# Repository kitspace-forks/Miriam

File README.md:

Miriam
========

Miriam is an open-source instrument for isothermal amplification reactions such as LAMP and realtime fluorescence detection. The costs per instrument are below 1000 USD, and our goal is to make it less expensive, more robust, and ready for volume production. It could be used as part of a test for Covid-19 😷.

**🔥 Update 2020 Oct 15 🔥** Updates are coming. We have built and tested a Miriam device and will be updating this repository with details soon. In the meantime, the new [BOM list](PCB/BOM) of the Covid-19 adapted Miriam is updated constantly during our test.

## User guide ##

View the [Miriam User Guide](https://docs.google.com/document/d/1WqGBbrccB8vQHHecIBe8Pv8aZ-rZUhXWWKjNA4fbFT0/edit?usp=sharing) as a Google Doc. Comments and suggestions are welcome.

## Help wanted

Currently, we are seeking help testing and improving the device. If you have skills circuit board layout, product design, software engineering, user interface design,  and thermal simulation, we could use your help. Furthermore, if you would like to collaborate to put this instrument to real world use, please file an issue or contact [Andrew Straw](<straw@bio.uni-freiburg.de>).

## License

Copyright Miroculus Inc.2016
Based on original work from Arduino (Sweden)

This documentation describes Open Hardware and is licensed under the CERN OHL v. 1.2.

Licensed under CERN OHL v.1.2

You may redistribute and modify this documentation under the terms of the [CERN OHL v.1.2.](http://ohwr.org/cernohl). This documentation is distributed WITHOUT ANY EXPRESS OR IMPLIED WARRANTY, INCLUDING OF MERCHANTABILITY, SATISFACTORY QUALITY AND FITNESS FOR A PARTICULAR PURPOSE. Please see the CERN OHL v.1.2 for applicable conditions

## Introduction

Miriam is optimized for the Syto 9 fluorescent intercalating DNA dye. (The original design was for [calcein dye](http://loopamp.eiken.co.jp/e/products/fluore/index.html). The selected LED is an angle SMD led with peak wavelength 461nm. The photodiode is an RGB photodiode most sensitive to green light. The optics also include an emission filter utilized in theatrical lighting.  The development and selection of components is further described in a [Master's thesis](http://lutpub.lut.fi/handle/10024/159386) done from miriam. 

**Figure 1.** LAMP reaction in 96 well plate. The reaction was performed in the center and corners of the 96 well plate to test heat uniformity.

In the performance testing of Miriam, the detection limit for DNA using LAMP as amplification platform has been 2amol in 10ul of sample (figure 1).

**Figure 2.** LAMP reaction with 2amol DNA input, fluorescence measured every 2 minutes (y, Normalized signal and x, cycle (2 min).

To report an issue, go to the [issues](http://github.com/strawlab/Miriam/issues) section

If you're interested in modifying or extending the Miriam platform, we strongly suggest you to send us an email discussing your ideas. That way you can coordinate with our team and others, giving your work a higher chance of being integrated into the official release.

## Design

The optics of Miriam plus are designed to support Syto9 + DNA. The emission and absorption spectra of Syto9 + DNA are represented in Figure 3.

**Figure 3.** Syto9+DNA emission and excitation spectra.

LEE filter 738 is used for blocking the excitation light. Whole optic design of Miriam plus is shown in Figure 4.

**Figure 4.** Optic design for Miriam plus to detect Syto9 + DNA.

The middle heating board and the LED and PD arrangements have been designed to support 96-well plates with the following dimensions (figure 5).

**Figure 5.** 96-well plate dimensions supported by Miriam

To control the heating of Miriam there are two heater PCBs. They have been designed so that in the middle is a 10 kohm SMD thermistor and the heat is generated by current flowing through the copper traces. These traces have been designed to be so long and narrow that they create an internal resistance of few ohms. The traces are closer to each other in the edges because heat is measured from the middle and the edges of the PCB boards meet ambient air and they need to produce more heat. (Figure 6.)

**Figure 6.** Heating plates, heat is generated by trace resistance. Right: The middle heater creating the temperature required for amplification (58-68 degrees C). Left: The top heater keeping vapor from condensing to the lid, kept at 80 degrees C. 

**Figure 6a.** The distribution of heat in the FR4 and Al heaters. FR4 heaters may work with small number of wells setup. For Miriam, we recommend using Al boards for better heat distribution.

Original Miriam design has 2.5 oC difference in temperature of the central wells and those on the far edge. Adding a heating wire on the edge of the lower heater can improve the uniformity (Fig. 6b). The temperature difference is reduced as low as 1oC or +/-0.5 oC by tuning the heat wire temperature (current) manually. An additional close-loop control for the heating wire would further improve the temperature uniformity.    

**Figure 6b.** Additional heat wire (left) helps to improve heat uniformity of the plate as in thermography images(right).

The heat uniformity of Miriam would be improved further by optimizing the heating traces of the heaters. Using a PCB thermal analysis software (Fig. 6C) with certain protocol for heat trace optimization would help to boost the design process.

**Figure 6c.** Heat distribution of the lower heater obtained from PCB thermal analysis software [(More detail of the analysis)](https://www.adam-research.de/en/2020/10/corona-forschung-mit-trm3/).

The detection of fluorescence is done with 96 LEDs and 96 photodiodes creating LED and photodiode PCBs. The LED peak wavelength is 470 nm and photodiode is a green RGB photodiode. The measured voltage is amplified with an operational amplifier to 0-5 V that is then converted by Arduino’s 8-bit ADC to be a numerical value. (figure 7.)

**Figure 7.** LED (left) and new photodiode (right) PCBs.

All of these boards are controlled by a shield that is directly mounted to the Arduino mega board (figure 8). The shield contains three MOSFETs to control LED board and the two heater boards, the required components to read the heat from the thermistors as well as a WIFI chip. The WIFI chip makes it possible for Arduino to be connected to a local WIFI and this way communicate autonomously to a web service.

**Figure 8.** The Arduino shield. 

Assembly
------------
3D print the printable parts under folder ["3D model"](3D%20Model), sand them if nescessary to make them align with each other. Assemble the boards as presented in the Figure 9. In the assembly cut with scissors the emission filter and glue to the filter holder.

**Figure 9.** Miriam assembly instruction. [High resolution version for printing](Miriam_assembly_guide.pdf) and [Video](https://youtu.be/ynIIGh6IMBA)

**Note:** All the cables used for Miriam must be "Opposite Side Contacts".
          For hand soldering, it is recommended to use solder paste and stencils for the sensor board. If it is possible, use reflow oven for the bottom side.
          
**Updated components:** The new [BOM list](PCB/BOM) of the Covid-19 adapted Miriam will be updated constantly during our test.

Software
------------
We just tested and improved the serial version of the software [Serial_003](Programs/Serial_003).

Improvement wish list
------------
A more robust type of connector can be considered. May change to 1mm pitch. 
Optimization for the traces of lower heater board to have uniformity heat distribution.

Credits
--------
The original Miriam is an open source project, supported by Miroculus in collaboration with Arduino (Sweden). The team was led by Juho Terrijarvi.

This version of Miriam has been improved by [Straw Lab](https://strawlab.org) to make it work with Syto-9 + DNA for potentially Covid-19 test.
Icon and image designed by Miroculus.

The PCB thermal analysis is performed by [ADAM research](https://www.adam-research.de/en/). 

Code of conduct
--------
Anyone who interacts with this software in any space, including but not limited
to this GitHub repository, must follow our [code of
conduct](code_of_conduct.md).

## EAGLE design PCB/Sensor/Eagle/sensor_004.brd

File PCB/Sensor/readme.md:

# Sensor_004
- Changed the order of power pins of the connector and the new footprint for new photodiode (TEMD6200FX01)

- material FR4
- 2 layer
- double sided assembly
- 1oz copper
- 1.6 mm thick
- Leadfree HAL
- Black soldermask
- White silkscreen

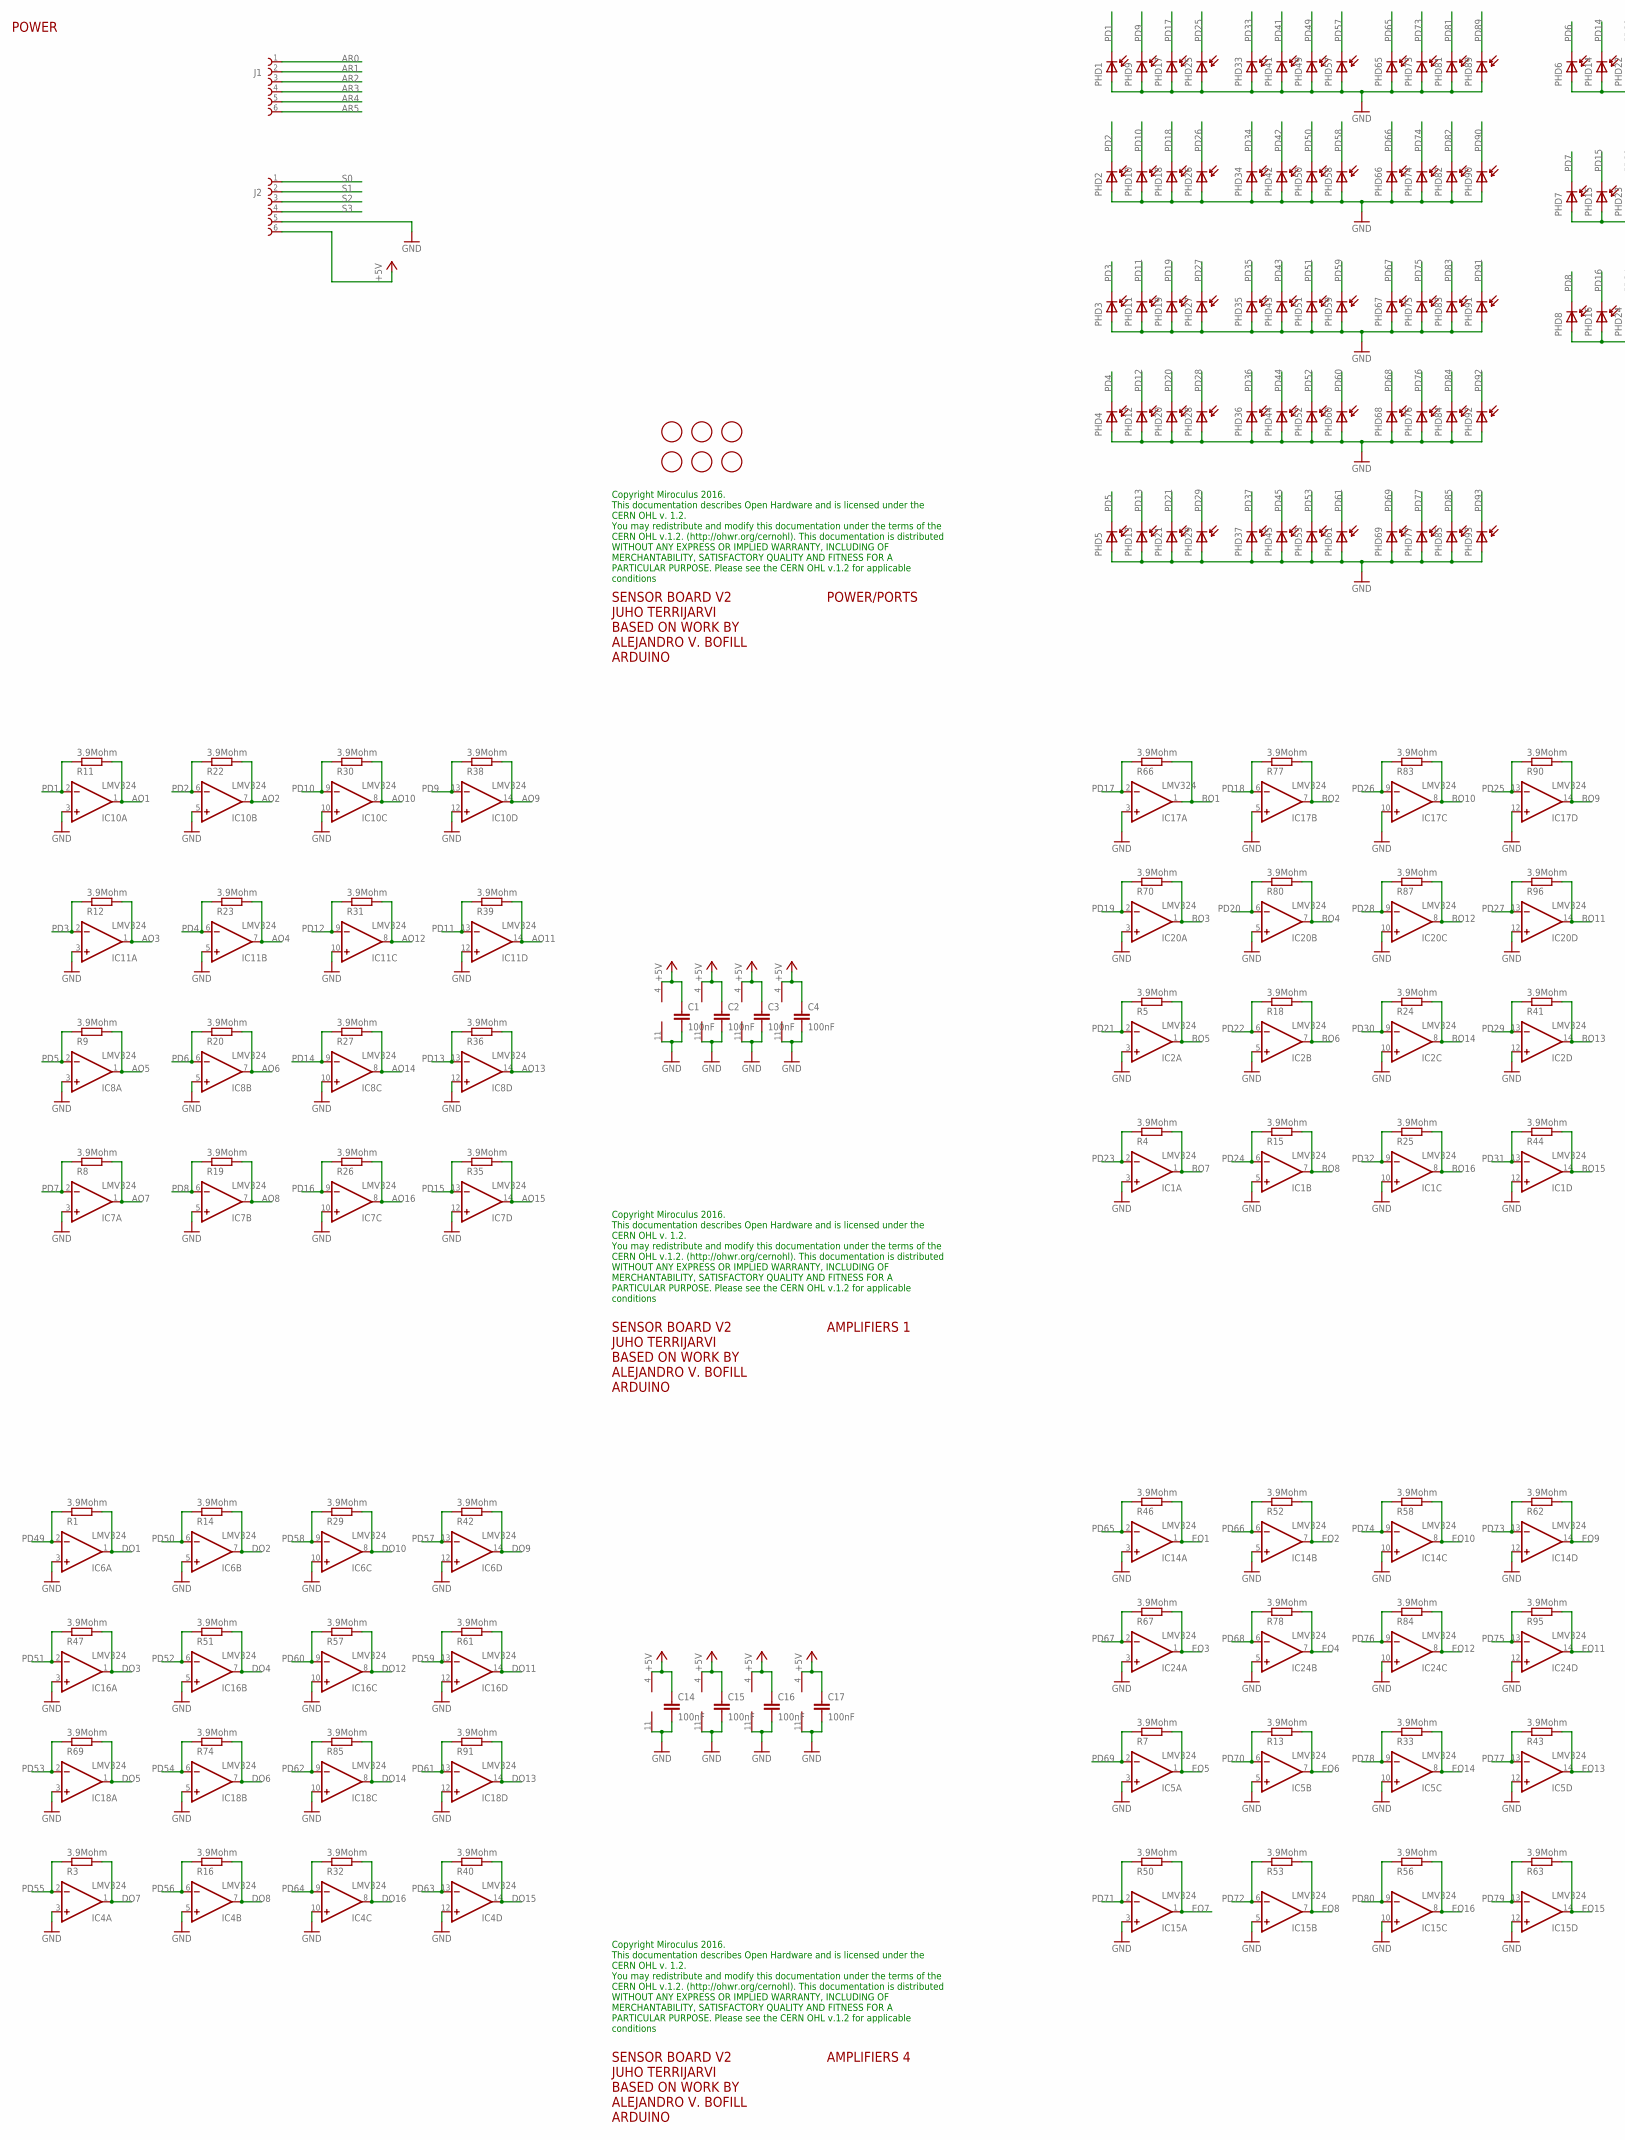
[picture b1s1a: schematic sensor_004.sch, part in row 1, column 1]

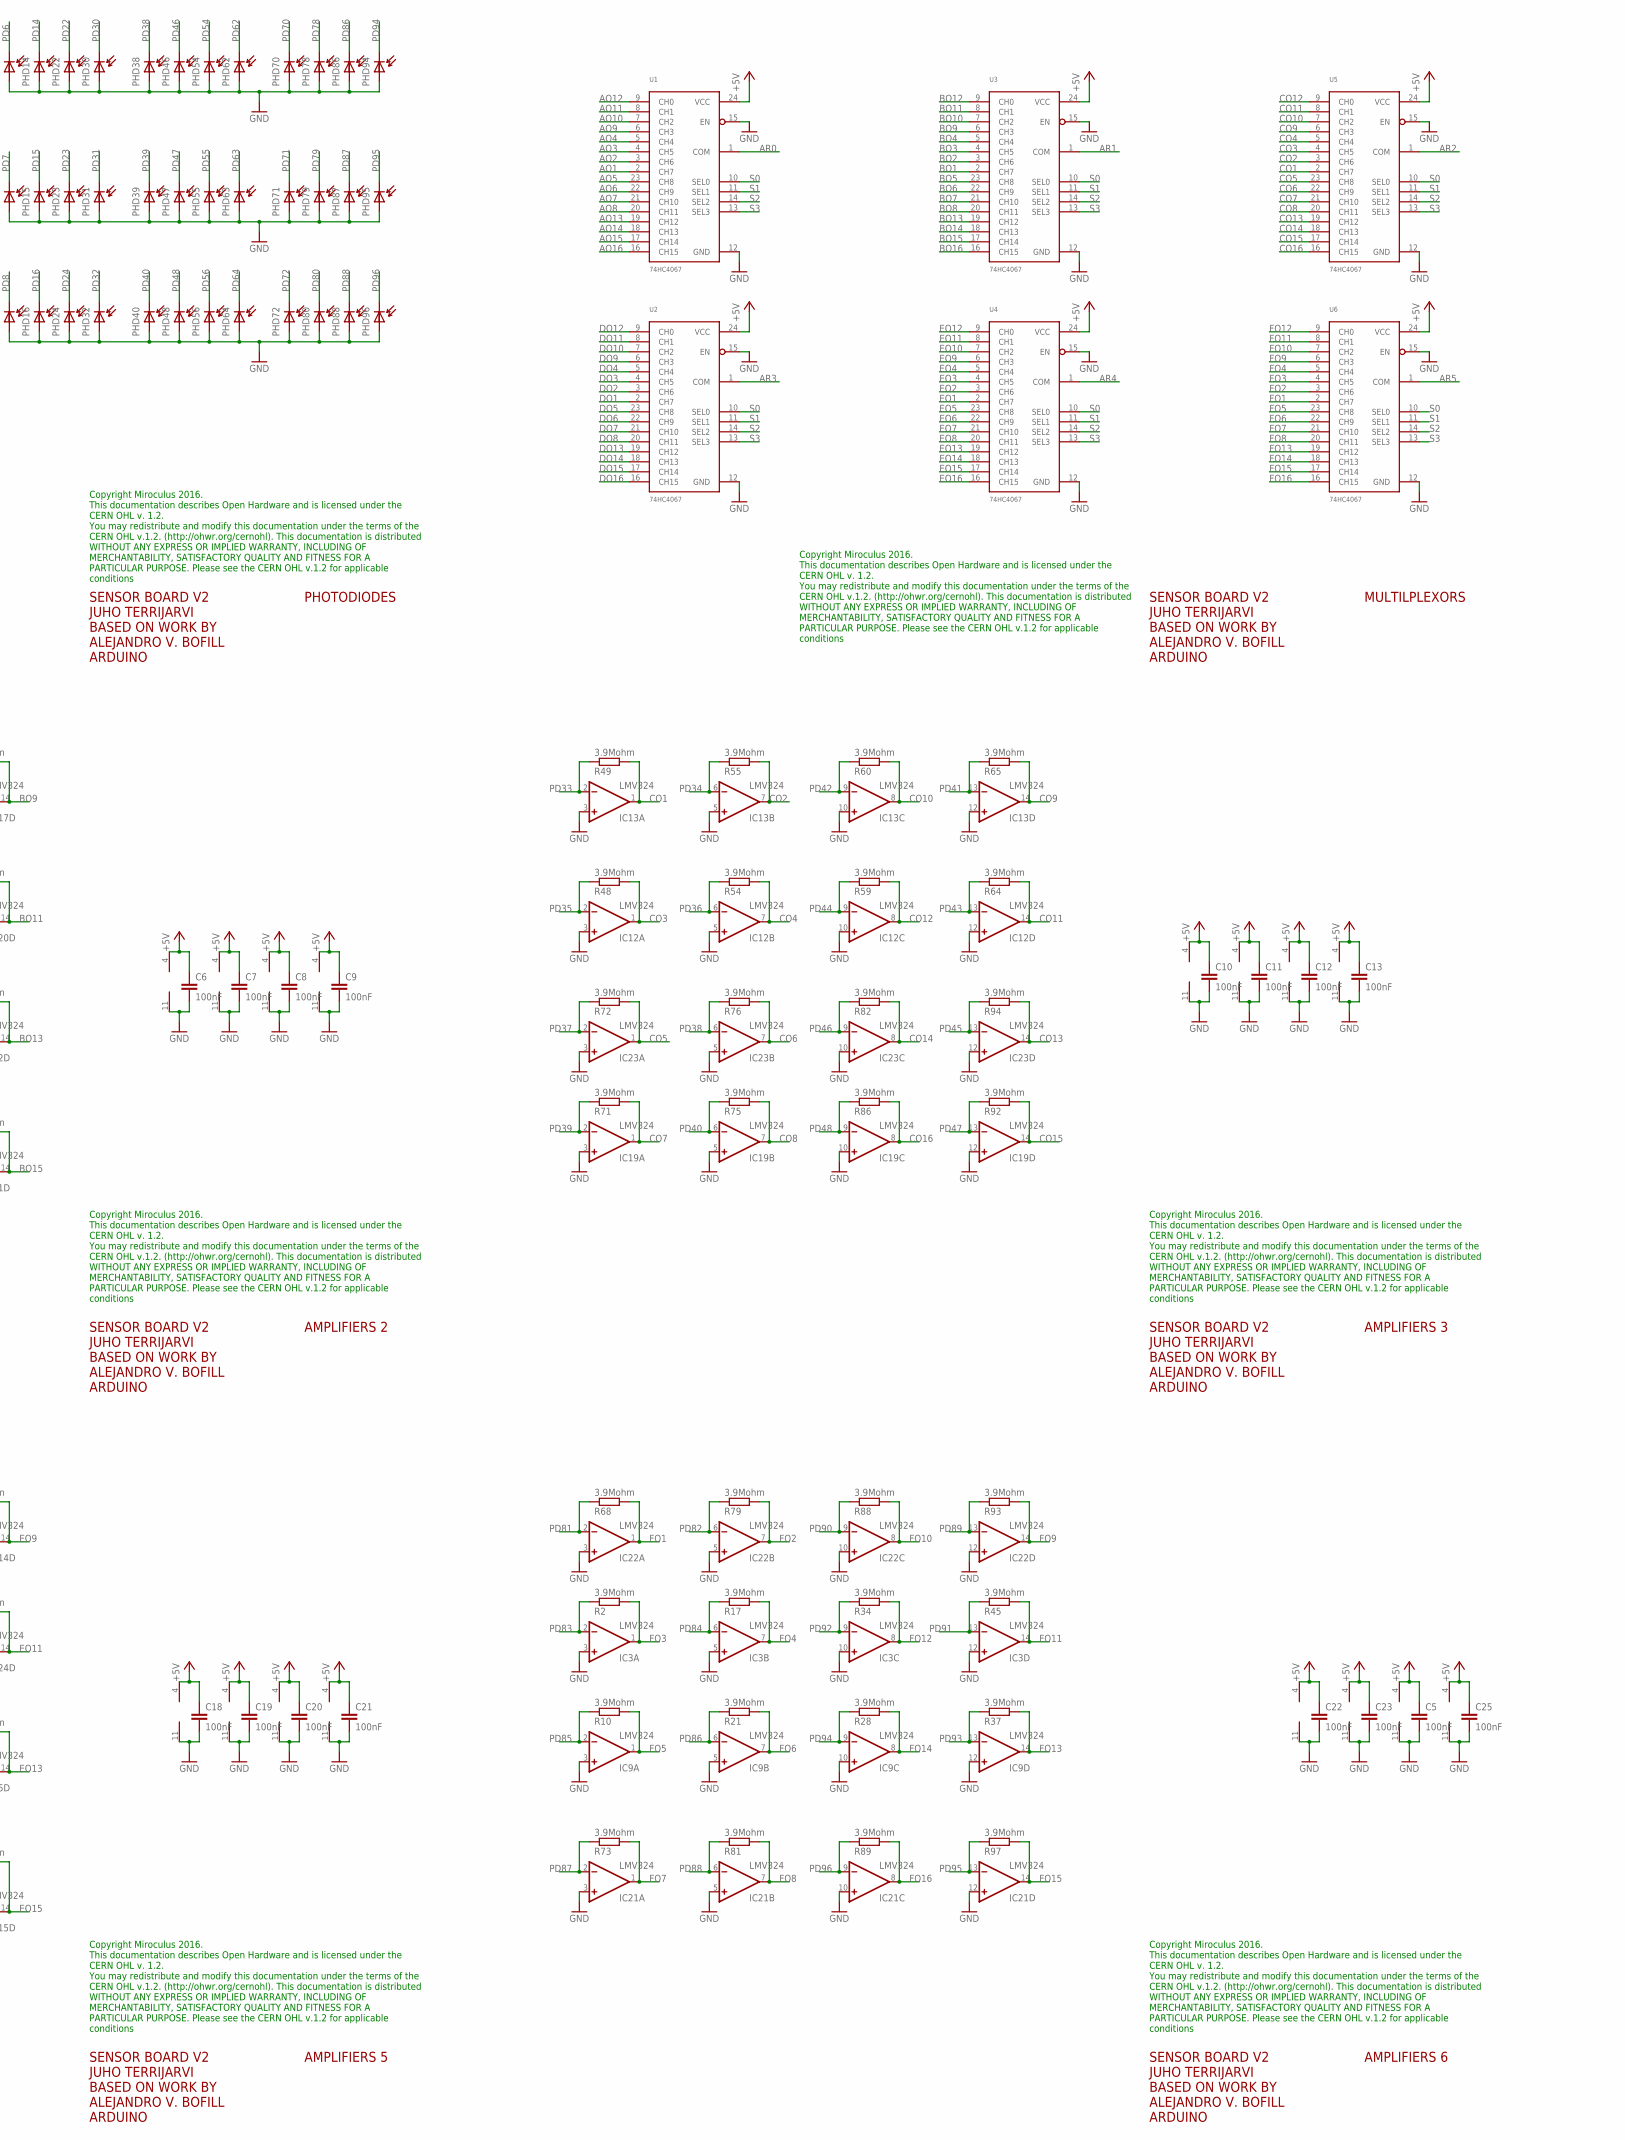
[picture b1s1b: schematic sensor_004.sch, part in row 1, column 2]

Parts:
C1, C2, C3, C4, C5, C6, C7, C8, C9, C10, C11, C12, C13, C14, C15, C16, C17, C18, C19, C20, C21, C22, C23, C25: 100nF; C0603
FD1, FD2, FD3, FD4, FD5, FD6: FIDUCIALMOUNT; FIDUCIA-MOUNT
IC1, IC2, IC3, IC4, IC5, IC6, IC7, IC8, IC9, IC10, IC11, IC12, IC13, IC14, IC15, IC16, IC17, IC18, IC19, IC20, IC21, IC22, IC23, IC24: LMV324; SO14
J1, J2: 68710614522
PHD1, PHD2, PHD3, PHD4, PHD5, PHD6, PHD7, PHD8, PHD9, PHD10, PHD11, PHD12, PHD13, PHD14, PHD15, PHD16, PHD17, PHD18, PHD19, PHD20, PHD21, PHD22, PHD23, PHD24, PHD25, PHD26, PHD27, PHD28, PHD29, PHD30, PHD31, PHD32, PHD33, PHD34, PHD35, PHD36, PHD37, PHD38, PHD39, PHD40, PHD41, PHD42, PHD43, PHD44, PHD45, PHD46, PHD47, PHD48, PHD49, PHD50, PHD51, PHD52, PHD53, PHD54, PHD55, PHD56, PHD57, PHD58, PHD59, PHD60, PHD61, PHD62, PHD63, PHD64, PHD65, PHD66, PHD67, PHD68, PHD69, PHD70, PHD71, PHD72, PHD73, PHD74, PHD75, PHD76, PHD77, PHD78, PHD79, PHD80, PHD81, PHD82, PHD83, PHD84, PHD85, PHD86, PHD87, PHD88, PHD89, PHD90, PHD91, PHD92, PHD93, PHD94, PHD95, PHD96: CLS15-22C/L213G/TR8; PD_2
R1, R2, R3, R4, R5, R7, R8, R9, R10, R11, R12, R13, R14, R15, R16, R17, R18, R19, R20, R21, R22, R23, R24, R25, R26, R27, R28, R29, R30, R31, R32, R33, R34, R35, R36, R37, R38, R39, R40, R41, R42, R43, R44, R45, R46, R47, R48, R49, R50, R51, R52, R53, R54, R55, R56, R57, R58, R59, R60, R61, R62, R63, R64, R65, R66, R67, R68, R69, R70, R71, R72, R73, R74, R75, R76, R77, R78, R79, R80, R81, R82, R83, R84, R85, R86, R87, R88, R89, R90, R91, R92, R93, R94, R95, R96, R97: 3.9Mohm; R0603
U1, U2, U3, U4, U5, U6: 74HC4067; SSOP24

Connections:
+5V: C1.1, C2.1, C3.1, C4.1, C5.1, C6.1, C7.1, C8.1, C9.1, C10.1, C11.1, C12.1, C13.1, C14.1, C15.1, C16.1, C17.1, C18.1, C19.1, C20.1, C21.1, C22.1, C23.1, C25.1, IC1.4 (V+), IC2.4 (V+), IC3.4 (V+), IC4.4 (V+), IC5.4 (V+), IC6.4 (V+), IC7.4 (V+), IC8.4 (V+), IC9.4 (V+), IC10.4 (V+), IC11.4 (V+), IC12.4 (V+), IC13.4 (V+), IC14.4 (V+), IC15.4 (V+), IC16.4 (V+), IC17.4 (V+), IC18.4 (V+), IC19.4 (V+), IC20.4 (V+), IC21.4 (V+), IC22.4 (V+), IC23.4 (V+), IC24.4 (V+), J2.6, U1.24 (VCC), U2.24 (VCC), U3.24 (VCC), U4.24 (VCC), U5.24 (VCC), U6.24 (VCC)
AO1: IC10.1 (OUT), R11.2, U1.2 (CH7)
AO2: IC10.7 (OUT), R22.2, U1.3 (CH6)
AO3: IC11.1 (OUT), R12.2, U1.4 (CH5)
AO4: IC11.7 (OUT), R23.2, U1.5 (CH4)
AO5: IC8.1 (OUT), R9.2, U1.23 (CH8)
AO6: IC8.7 (OUT), R20.2, U1.22 (CH9)
AO7: IC7.1 (OUT), R8.2, U1.21 (CH10)
AO8: IC7.7 (OUT), R19.2, U1.20 (CH11)
AO9: IC10.14 (OUT), R38.2, U1.6 (CH3)
AO10: IC10.8 (OUT), R30.2, U1.7 (CH2)
AO11: IC11.14 (OUT), R39.2, U1.8 (CH1)
AO12: IC11.8 (OUT), R31.2, U1.9 (CH0)
AO13: IC8.14 (OUT), R36.2, U1.19 (CH12)
AO14: IC8.8 (OUT), R27.2, U1.18 (CH13)
AO15: IC7.14 (OUT), R35.2, U1.17 (CH14)
AO16: IC7.8 (OUT), R26.2, U1.16 (CH15)
AR0: J1.1, U1.1 (COM)
AR1: J1.2, U3.1 (COM)
AR2: J1.3, U5.1 (COM)
AR3: J1.4, U2.1 (COM)
AR4: J1.5, U4.1 (COM)
AR5: J1.6, U6.1 (COM)
BO1: IC17.1 (OUT), R66.2, U3.2 (CH7)
BO2: IC17.7 (OUT), R77.2, U3.3 (CH6)
BO3: IC20.1 (OUT), R70.2, U3.4 (CH5)
BO4: IC20.7 (OUT), R80.2, U3.5 (CH4)
BO5: IC2.1 (OUT), R5.2, U3.23 (CH8)
BO6: IC2.7 (OUT), R18.2, U3.22 (CH9)
BO7: IC1.1 (OUT), R4.2, U3.21 (CH10)
BO8: IC1.7 (OUT), R15.2, U3.20 (CH11)
BO9: IC17.14 (OUT), R90.2, U3.6 (CH3)
BO10: IC17.8 (OUT), R83.2, U3.7 (CH2)
BO11: IC20.14 (OUT), R96.2, U3.8 (CH1)
BO12: IC20.8 (OUT), R87.2, U3.9 (CH0)
BO13: IC2.14 (OUT), R41.2, U3.19 (CH12)
BO14: IC2.8 (OUT), R24.2, U3.18 (CH13)
BO15: IC1.14 (OUT), R44.2, U3.17 (CH14)
BO16: IC1.8 (OUT), R25.2, U3.16 (CH15)
CO1: IC13.1 (OUT), R49.2, U5.2 (CH7)
CO2: IC13.7 (OUT), R55.2, U5.3 (CH6)
CO3: IC12.1 (OUT), R48.2, U5.4 (CH5)
CO4: IC12.7 (OUT), R54.2, U5.5 (CH4)
CO5: IC23.1 (OUT), R72.2, U5.23 (CH8)
CO6: IC23.7 (OUT), R76.2, U5.22 (CH9)
CO7: IC19.1 (OUT), R71.2, U5.21 (CH10)
CO8: IC19.7 (OUT), R75.2, U5.20 (CH11)
CO9: IC13.14 (OUT), R65.2, U5.6 (CH3)
CO10: IC13.8 (OUT), R60.2, U5.7 (CH2)
CO11: IC12.14 (OUT), R64.2, U5.8 (CH1)
CO12: IC12.8 (OUT), R59.2, U5.9 (CH0)
CO13: IC23.14 (OUT), R94.2, U5.19 (CH12)
CO14: IC23.8 (OUT), R82.2, U5.18 (CH13)
CO15: IC19.14 (OUT), R92.2, U5.17 (CH14)
CO16: IC19.8 (OUT), R86.2, U5.16 (CH15)
DO1: IC6.1 (OUT), R1.2, U2.2 (CH7)
DO2: IC6.7 (OUT), R14.2, U2.3 (CH6)
DO3: IC16.1 (OUT), R47.2, U2.4 (CH5)
DO4: IC16.7 (OUT), R51.2, U2.5 (CH4)
DO5: IC18.1 (OUT), R69.2, U2.23 (CH8)
DO6: IC18.7 (OUT), R74.2, U2.22 (CH9)
DO7: IC4.1 (OUT), R3.2, U2.21 (CH10)
DO8: IC4.7 (OUT), R16.2, U2.20 (CH11)
DO9: IC6.14 (OUT), R42.2, U2.6 (CH3)
DO10: IC6.8 (OUT), R29.2, U2.7 (CH2)
DO11: IC16.14 (OUT), R61.2, U2.8 (CH1)
DO12: IC16.8 (OUT), R57.2, U2.9 (CH0)
DO13: IC18.14 (OUT), R91.2, U2.19 (CH12)
DO14: IC18.8 (OUT), R85.2, U2.18 (CH13)
DO15: IC4.14 (OUT), R40.2, U2.17 (CH14)
DO16: IC4.8 (OUT), R32.2, U2.16 (CH15)
EO1: IC14.1 (OUT), R46.2, U4.2 (CH7)
EO2: IC14.7 (OUT), R52.2, U4.3 (CH6)
EO3: IC24.1 (OUT), R67.2, U4.4 (CH5)
EO4: IC24.7 (OUT), R78.2, U4.5 (CH4)
EO5: IC5.1 (OUT), R7.2, U4.23 (CH8)
EO6: IC5.7 (OUT), R13.2, U4.22 (CH9)
EO7: IC15.1 (OUT), R50.2, U4.21 (CH10)
EO8: IC15.7 (OUT), R53.2, U4.20 (CH11)
EO9: IC14.14 (OUT), R62.2, U4.6 (CH3)
EO10: IC14.8 (OUT), R58.2, U4.7 (CH2)
EO11: IC24.14 (OUT), R95.2, U4.8 (CH1)
EO12: IC24.8 (OUT), R84.2, U4.9 (CH0)
EO13: IC5.14 (OUT), R43.2, U4.19 (CH12)
EO14: IC5.8 (OUT), R33.2, U4.18 (CH13)
EO15: IC15.14 (OUT), R63.2, U4.17 (CH14)
EO16: IC15.8 (OUT), R56.2, U4.16 (CH15)
FO1: IC22.1 (OUT), R68.2, U6.2 (CH7)
FO2: IC22.7 (OUT), R79.2, U6.3 (CH6)
FO3: IC3.1 (OUT), R2.2, U6.4 (CH5)
FO4: IC3.7 (OUT), R17.2, U6.5 (CH4)
FO5: IC9.1 (OUT), R10.2, U6.23 (CH8)
FO6: IC9.7 (OUT), R21.2, U6.22 (CH9)
FO7: IC21.1 (OUT), R73.2, U6.21 (CH10)
FO8: IC21.7 (OUT), R81.2, U6.20 (CH11)
FO9: IC22.14 (OUT), R93.2, U6.6 (CH3)
FO10: IC22.8 (OUT), R88.2, U6.7 (CH2)
FO11: IC3.14 (OUT), R45.2, U6.8 (CH1)
FO12: IC3.8 (OUT), R34.2, U6.9 (CH0)
FO13: IC9.14 (OUT), R37.2, U6.19 (CH12)
FO14: IC9.8 (OUT), R28.2, U6.18 (CH13)
FO15: IC21.14 (OUT), R97.2, U6.17 (CH14)
FO16: IC21.8 (OUT), R89.2, U6.16 (CH15)
GND: C1.2, C2.2, C3.2, C4.2, C5.2, C6.2, C7.2, C8.2, C9.2, C10.2, C11.2, C12.2, C13.2, C14.2, C15.2, C16.2, C17.2, C18.2, C19.2, C20.2, C21.2, C22.2, C23.2, C25.2, IC1.3 (+IN), IC1.5 (+IN), IC1.10 (+IN), IC1.11 (V-), IC1.12 (+IN), IC2.3 (+IN), IC2.5 (+IN), IC2.10 (+IN), IC2.11 (V-), IC2.12 (+IN), IC3.3 (+IN), IC3.5 (+IN), IC3.10 (+IN), IC3.11 (V-), IC3.12 (+IN), IC4.3 (+IN), IC4.5 (+IN), IC4.10 (+IN), IC4.11 (V-), IC4.12 (+IN), IC5.3 (+IN), IC5.5 (+IN), IC5.10 (+IN), IC5.11 (V-), IC5.12 (+IN), IC6.3 (+IN), IC6.5 (+IN), IC6.10 (+IN), IC6.11 (V-), IC6.12 (+IN), IC7.3 (+IN), IC7.5 (+IN), IC7.10 (+IN), IC7.11 (V-), IC7.12 (+IN), IC8.3 (+IN), IC8.5 (+IN), IC8.10 (+IN), IC8.11 (V-), IC8.12 (+IN), IC9.3 (+IN), IC9.5 (+IN), IC9.10 (+IN), IC9.11 (V-), IC9.12 (+IN), IC10.3 (+IN), IC10.5 (+IN), IC10.10 (+IN), IC10.11 (V-), IC10.12 (+IN), IC11.3 (+IN), IC11.5 (+IN), IC11.10 (+IN), IC11.11 (V-), IC11.12 (+IN), IC12.3 (+IN), IC12.5 (+IN), IC12.10 (+IN), IC12.11 (V-), IC12.12 (+IN), IC13.3 (+IN), IC13.5 (+IN), IC13.10 (+IN), IC13.11 (V-), IC13.12 (+IN), IC14.3 (+IN), IC14.5 (+IN), IC14.10 (+IN), IC14.11 (V-), IC14.12 (+IN), IC15.3 (+IN), IC15.5 (+IN), IC15.10 (+IN), IC15.11 (V-), IC15.12 (+IN), IC16.3 (+IN), IC16.5 (+IN), IC16.10 (+IN), IC16.11 (V-), IC16.12 (+IN), IC17.3 (+IN), IC17.5 (+IN), IC17.10 (+IN), IC17.11 (V-), IC17.12 (+IN), IC18.3 (+IN), IC18.5 (+IN), IC18.10 (+IN), IC18.11 (V-), IC18.12 (+IN), IC19.3 (+IN), IC19.5 (+IN), IC19.10 (+IN), IC19.11 (V-), IC19.12 (+IN), IC20.3 (+IN), IC20.5 (+IN), IC20.10 (+IN), IC20.11 (V-), IC20.12 (+IN), IC21.3 (+IN), IC21.5 (+IN), IC21.10 (+IN), IC21.11 (V-), IC21.12 (+IN), IC22.3 (+IN), IC22.5 (+IN), IC22.10 (+IN), IC22.11 (V-), IC22.12 (+IN), IC23.3 (+IN), IC23.5 (+IN), IC23.10 (+IN), IC23.11 (V-), IC23.12 (+IN), IC24.3 (+IN), IC24.5 (+IN), IC24.10 (+IN), IC24.11 (V-), IC24.12 (+IN), J2.5, PHD1.1, PHD2.1, PHD3.1, PHD4.1, PHD5.1, PHD6.1, PHD7.1, PHD8.1, PHD9.1, PHD10.1, PHD11.1, PHD12.1, PHD13.1, PHD14.1, PHD15.1, PHD16.1, PHD17.1, PHD18.1, PHD19.1, PHD20.1, PHD21.1, PHD22.1, PHD23.1, PHD24.1, PHD25.1, PHD26.1, PHD27.1, PHD28.1, PHD29.1, PHD30.1, PHD31.1, PHD32.1, PHD33.1, PHD34.1, PHD35.1, PHD36.1, PHD37.1, PHD38.1, PHD39.1, PHD40.1, PHD41.1, PHD42.1, PHD43.1, PHD44.1, PHD45.1, PHD46.1, PHD47.1, PHD48.1, PHD49.1, PHD50.1, PHD51.1, PHD52.1, PHD53.1, PHD54.1, PHD55.1, PHD56.1, PHD57.1, PHD58.1, PHD59.1, PHD60.1, PHD61.1, PHD62.1, PHD63.1, PHD64.1, PHD65.1, PHD66.1, PHD67.1, PHD68.1, PHD69.1, PHD70.1, PHD71.1, PHD72.1, PHD73.1, PHD74.1, PHD75.1, PHD76.1, PHD77.1, PHD78.1, PHD79.1, PHD80.1, PHD81.1, PHD82.1, PHD83.1, PHD84.1, PHD85.1, PHD86.1, PHD87.1, PHD88.1, PHD89.1, PHD90.1, PHD91.1, PHD92.1, PHD93.1, PHD94.1, PHD95.1, PHD96.1, U1.12 (GND), U1.15 (EN), U2.12 (GND), U2.15 (EN), U3.12 (GND), U3.15 (EN), U4.12 (GND), U4.15 (EN), U5.12 (GND), U5.15 (EN), U6.12 (GND), U6.15 (EN)
PD1: IC10.2 (-IN), PHD1.2, R11.1
PD2: IC10.6 (-IN), PHD2.2, R22.1
PD3: IC11.2 (-IN), PHD3.2, R12.1
PD4: IC11.6 (-IN), PHD4.2, R23.1
PD5: IC8.2 (-IN), PHD5.2, R9.1
PD6: IC8.6 (-IN), PHD6.2, R20.1
PD7: IC7.2 (-IN), PHD7.2, R8.1
PD8: IC7.6 (-IN), PHD8.2, R19.1
PD9: IC10.13 (-IN), PHD9.2, R38.1
PD10: IC10.9 (-IN), PHD10.2, R30.1
PD11: IC11.13 (-IN), PHD11.2, R39.1
PD12: IC11.9 (-IN), PHD12.2, R31.1
PD13: IC8.13 (-IN), PHD13.2, R36.1
PD14: IC8.9 (-IN), PHD14.2, R27.1
PD15: IC7.13 (-IN), PHD15.2, R35.1
PD16: IC7.9 (-IN), PHD16.2, R26.1
PD17: IC17.2 (-IN), PHD17.2, R66.1
PD18: IC17.6 (-IN), PHD18.2, R77.1
PD19: IC20.2 (-IN), PHD19.2, R70.1
PD20: IC20.6 (-IN), PHD20.2, R80.1
PD21: IC2.2 (-IN), PHD21.2, R5.1
PD22: IC2.6 (-IN), PHD22.2, R18.1
PD23: IC1.2 (-IN), PHD23.2, R4.1
PD24: IC1.6 (-IN), PHD24.2, R15.1
PD25: IC17.13 (-IN), PHD25.2, R90.1
PD26: IC17.9 (-IN), PHD26.2, R83.1
PD27: IC20.13 (-IN), PHD27.2, R96.1
PD28: IC20.9 (-IN), PHD28.2, R87.1
PD29: IC2.13 (-IN), PHD29.2, R41.1
PD30: IC2.9 (-IN), PHD30.2, R24.1
PD31: IC1.13 (-IN), PHD31.2, R44.1
PD32: IC1.9 (-IN), PHD32.2, R25.1
PD33: IC13.2 (-IN), PHD33.2, R49.1
PD34: IC13.6 (-IN), PHD34.2, R55.1
PD35: IC12.2 (-IN), PHD35.2, R48.1
PD36: IC12.6 (-IN), PHD36.2, R54.1
PD37: IC23.2 (-IN), PHD37.2, R72.1
PD38: IC23.6 (-IN), PHD38.2, R76.1
PD39: IC19.2 (-IN), PHD39.2, R71.1
PD40: IC19.6 (-IN), PHD40.2, R75.1
PD41: IC13.13 (-IN), PHD41.2, R65.1
PD42: IC13.9 (-IN), PHD42.2, R60.1
PD43: IC12.13 (-IN), PHD43.2, R64.1
PD44: IC12.9 (-IN), PHD44.2, R59.1
PD45: IC23.13 (-IN), PHD45.2, R94.1
PD46: IC23.9 (-IN), PHD46.2, R82.1
PD47: IC19.13 (-IN), PHD47.2, R92.1
PD48: IC19.9 (-IN), PHD48.2, R86.1
PD49: IC6.2 (-IN), PHD49.2, R1.1
PD50: IC6.6 (-IN), PHD50.2, R14.1
PD51: IC16.2 (-IN), PHD51.2, R47.1
PD52: IC16.6 (-IN), PHD52.2, R51.1
PD53: IC18.2 (-IN), PHD53.2, R69.1
PD54: IC18.6 (-IN), PHD54.2, R74.1
PD55: IC4.2 (-IN), PHD55.2, R3.1
PD56: IC4.6 (-IN), PHD56.2, R16.1
PD57: IC6.13 (-IN), PHD57.2, R42.1
PD58: IC6.9 (-IN), PHD58.2, R29.1
PD59: IC16.13 (-IN), PHD59.2, R61.1
PD60: IC16.9 (-IN), PHD60.2, R57.1
PD61: IC18.13 (-IN), PHD61.2, R91.1
PD62: IC18.9 (-IN), PHD62.2, R85.1
PD63: IC4.13 (-IN), PHD63.2, R40.1
PD64: IC4.9 (-IN), PHD64.2, R32.1
PD65: IC14.2 (-IN), PHD65.2, R46.1
PD66: IC14.6 (-IN), PHD66.2, R52.1
PD67: IC24.2 (-IN), PHD67.2, R67.1
PD68: IC24.6 (-IN), PHD68.2, R78.1
PD69: IC5.2 (-IN), PHD69.2, R7.1
PD70: IC5.6 (-IN), PHD70.2, R13.1
PD71: IC15.2 (-IN), PHD71.2, R50.1
PD72: IC15.6 (-IN), PHD72.2, R53.1
PD73: IC14.13 (-IN), PHD73.2, R62.1
PD74: IC14.9 (-IN), PHD74.2, R58.1
PD75: IC24.13 (-IN), PHD75.2, R95.1
PD76: IC24.9 (-IN), PHD76.2, R84.1
PD77: IC5.13 (-IN), PHD77.2, R43.1
PD78: IC5.9 (-IN), PHD78.2, R33.1
PD79: IC15.13 (-IN), PHD79.2, R63.1
PD80: IC15.9 (-IN), PHD80.2, R56.1
PD81: IC22.2 (-IN), PHD81.2, R68.1
PD82: IC22.6 (-IN), PHD82.2, R79.1
PD83: IC3.2 (-IN), PHD83.2, R2.1
PD84: IC3.6 (-IN), PHD84.2, R17.1
PD85: IC9.2 (-IN), PHD85.2, R10.1
PD86: IC9.6 (-IN), PHD86.2, R21.1
PD87: IC21.2 (-IN), PHD87.2, R73.1
PD88: IC21.6 (-IN), PHD88.2, R81.1
PD89: IC22.13 (-IN), PHD89.2, R93.1
PD90: IC22.9 (-IN), PHD90.2, R88.1
PD91: IC3.13 (-IN), PHD91.2, R45.1
PD92: IC3.9 (-IN), PHD92.2, R34.1
PD93: IC9.13 (-IN), PHD93.2, R37.1
PD94: IC9.9 (-IN), PHD94.2, R28.1
PD95: IC21.13 (-IN), PHD95.2, R97.1
PD96: IC21.9 (-IN), PHD96.2, R89.1
S0: J2.1, U1.10 (SEL0), U2.10 (SEL0), U3.10 (SEL0), U4.10 (SEL0), U5.10 (SEL0), U6.10 (SEL0)
S1: J2.2, U1.11 (SEL1), U2.11 (SEL1), U3.11 (SEL1), U4.11 (SEL1), U5.11 (SEL1), U6.11 (SEL1)
S2: J2.3, U1.14 (SEL2), U2.14 (SEL2), U3.14 (SEL2), U4.14 (SEL2), U5.14 (SEL2), U6.14 (SEL2)
S3: J2.4, U1.13 (SEL3), U2.13 (SEL3), U3.13 (SEL3), U4.13 (SEL3), U5.13 (SEL3), U6.13 (SEL3)

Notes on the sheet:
SENSOR BOARD V2 JUHO TERRIJARVI BASED ON WORK BY ALEJANDRO V. BOFILL ARDUINO
POWER
POWER/PORTS
PHOTODIODES
AMPLIFIERS 1
AMPLIFIERS 2
AMPLIFIERS 3
AMPLIFIERS 4
AMPLIFIERS 5
AMPLIFIERS 6
MULTILPLEXORS
Copyright Miroculus 2016. This documentation describes Open Hardware and is licensed under the CERN OHL v. 1.2. You may redistribute and modify this documentation under the terms of the CERN OHL v.1.2. (http://ohwr.org/cernohl). This documentation is distributed WITHOUT ANY EXPRESS OR IMPLIED WARRA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

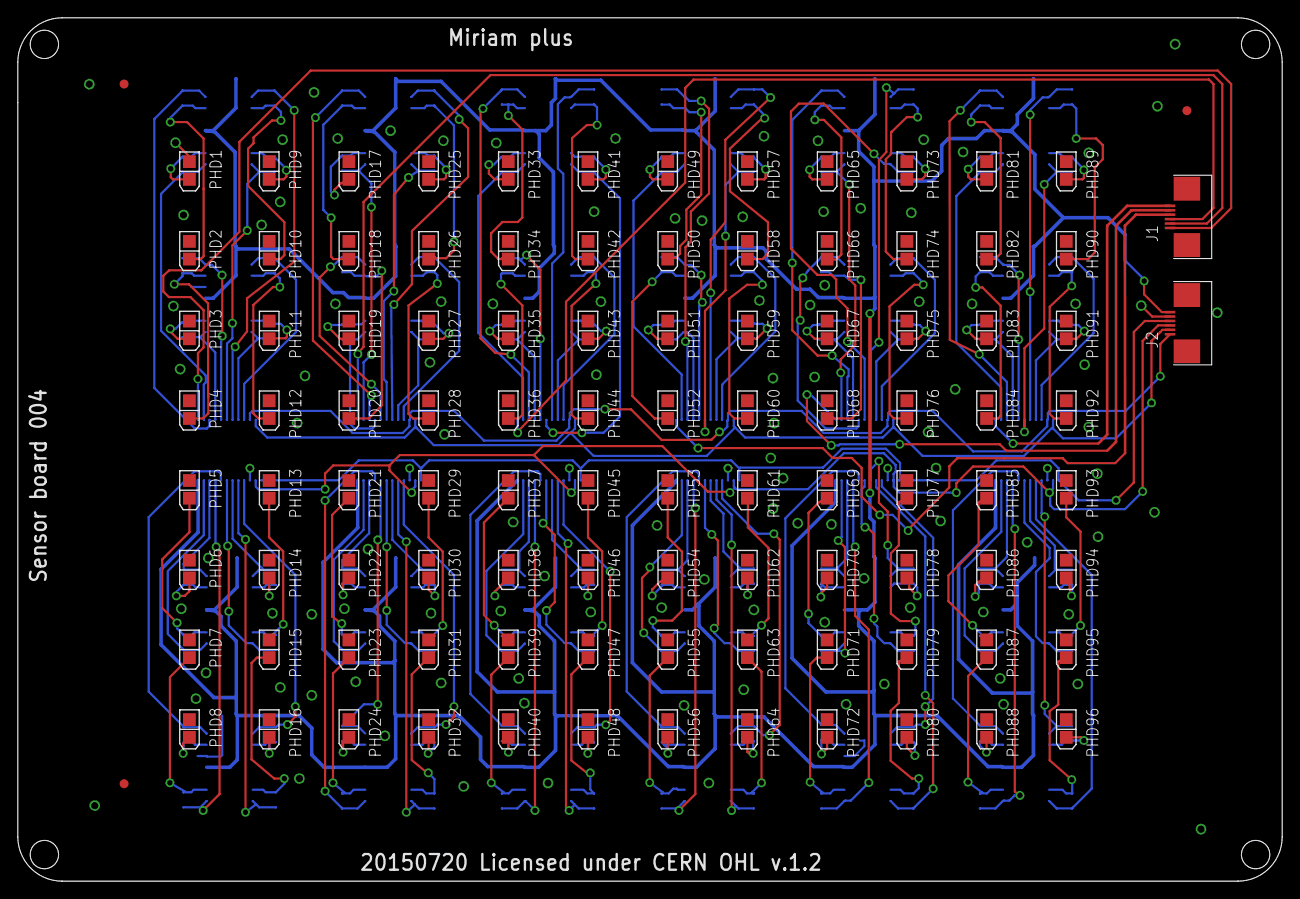
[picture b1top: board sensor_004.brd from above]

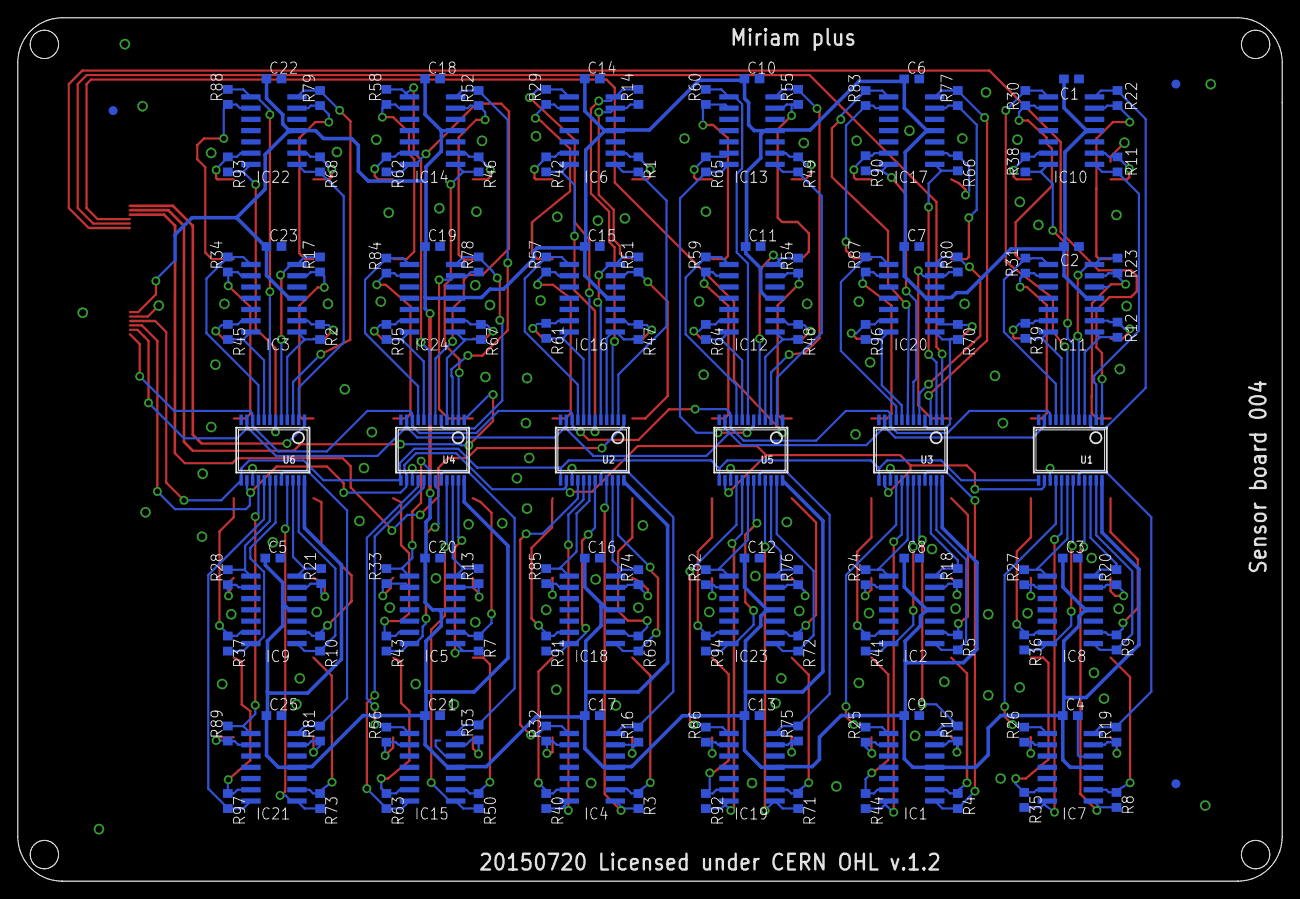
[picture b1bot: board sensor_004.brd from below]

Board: 2 copper layers, 142.8 x 97.5 mm, 254 parts (153 on the bottom side), 204 nets.

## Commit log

2020-08-27 autofill cell names A1->H12; change the hardcoded time between the readouts
2020-08-27 ignore .vs, obj. debug, bin folders
2020-08-28 reverse columns order on the plate (was incorrect)
2020-08-30 sensor2 wiring and FR4 heaters
2020-09-01 rearrange columns differently
    sequence from serial port: A11,A12,A9,A10,....,A1,A2, ...
2020-09-03 added the inter-measure interval setting (in seconds)
2020-09-03 write time of measurement to csv file
2020-09-03 reading from csv works (now filename is hardcoded, and the csv is assumed to be correctly formatted
2020-09-04 well names are stored in .cells.tsv file near the exe; added buttons to autofill and clear all names
2020-09-07 save csv to the app folder with filename miriam_datetime.csv
2020-09-09 update optic design for Syto9+DNA
2020-10-01 change sensor board and case
2020-10-01 add heat distribution
2020-10-08 make the settings persistent (store in app settings)
2020-10-08 ignore .cells.tsv file (generated automatically)
2020-10-08 beutify plot
    Yellow color replaced by Chocolate; the figure panel is resized with the form
2020-10-08 built release for the last changes
2020-10-08 remove unnecessary file
2020-10-15 add link to code of conduct
2020-10-15 fix layout
2020-10-15 add heat uniformity
2020-10-15 add heat_simulation
2020-10-22 added new arduino file
2020-10-22 cancel heating on exit
2020-10-23 ino:changed the temperature readout formula for A11 (TH_EXTRA)
2020-10-23 ino: changed order of 'i' output to be backward compatible
2020-10-23 fix typo
2020-10-23 reading temperatures with dicts, refactor arduino commands
2020-10-23 changed design for additional sensors; more refactoring for arduino readouts
2020-10-30 (ino) changed linear correction in temperature calculation
2020-10-30 Set EXTRA_HEAT to MANUAL when stop heating
2020-11-02 serial005.ino: with sound alarm and status LED (not finished)
2020-11-04 ino: extract mystatusled class description
2020-11-04 ino: editable box temperature threshold
2020-11-04 fix cancel on exit
2020-11-04 changed icon
2020-11-05 rebuild
2020-11-06 link to user guide in README
2020-11-06 RT-LAMP with Miriam flow
2020-11-06 Add assembly guide and new box
2020-11-06 correct link
2020-11-09 update BOM list
2020-11-13 fix heat canceling
2020-11-13 added box temperature threshold setting
2020-11-13 changed default settings
2020-11-19 cleaning attempt
2020-11-19 rebuilt with new icon; remove unnecessary files
2020-11-19 change calibration function of the thermistor
2020-11-25 make arduino PID_v1 library comply with spec
    See https://arduino.github.io/arduino-cli/latest/library-specification/
2020-11-25 update BOM
2020-11-25 change GUI figure
2020-11-25 replaced icon
2020-11-25 fixed programs readme
2020-11-25 Update SW/FW combinations in Serial Readme
2020-11-25 add continuous integration using github actions
    So far, this builds the Windows program and the Arduino firmware.
2020-11-25 add link to CI build in README
2020-11-28 adjust figure posiiton
2020-11-28 update BOM link
2020-12-02 write to csv live, removed last comma from all rows
2020-12-04 add melting function
2020-12-07 update BOM readme
2020-12-08 + form with melting settings; storing them in app settings; melting func not tested in reality; ino: add melting to list of states
2020-12-08 fixed filename format to yyyymmdd...
2020-12-09 fix melting stopping
2020-12-09 fixed float convertion bug; add tolerance parameter for melting
2020-12-09 ci: store artifact attempt
2020-12-09 rearrange for better time intervals
2020-12-09 +setting melting on/off
2020-12-11 fix temperature threshold check
2020-12-14 update melting tune
2020-12-22 added the controls to the form
2020-12-28 moved measurement settings
2020-12-29 moved folder setting
2020-12-29 + filename prefix setting
2021-01-11 update melt tuning
2021-01-11 start melting commands sequence changed
2021-01-12 add melt_init
2021-01-12 add melt init on software side
2021-01-12 debug arduino artifact building
2021-01-12 update name of zip file created in build step
2021-01-12 update job names
2021-01-12 Add PID output values to CSV
2021-01-12 Remove .exe file
    This executable is now built in Github Actions with every commit. We
    will also publish it using the Github release system upon each release.
    As discussed in
    https://github.com/strawlab/Miriam/issues/8#issuecomment-752925917 , I
    am removing the compiled .exe from the source code repository.
2021-01-14 add firmware version: 0.1.0
2021-01-15 +software version; version check; fix timeout (back to 500); set version numbers to 2.0.0
2021-01-17 save data to tsv with metadata
2021-01-17 fix string<->double convertion
2021-01-19 ino: float input of temperature settings
2021-01-19 fix applying tolerance setting
2021-01-19 save csv: comma-separated, metadata 2 strings
2021-01-19 fix exception handling during version check
2021-01-20 ensure convertion of decimal numbers works everywhere
2021-01-20 refactoring
2021-01-27 update melt parameters
2021-02-03 renamed columns in the csv
2021-02-04 smarter exception handling for version check
2021-02-04 fix error message
2021-02-09 package arduino source with .exe
2021-02-10 update docs
2021-02-24 reformat code
2021-02-24 add comments. code should run the same.
2021-02-24 clear ADCs and multiplexers before reads
2021-02-24 attempt to increase dynamic range
2021-02-26 perform ADC reads 500 microseconds after LED on
    We measured with an oscilloscope that the voltage coming into the analog
    input of the arduino rises over about 250 microseconds to a plateau.
    This should ensure that we are measuring the plateau level.
2021-02-26 save settings in yaml format to csv as a comment
2021-03-02 import/export yaml measurement settings
2021-03-02 add packages config file
2021-03-02 removed unnecessary file from compile
2021-03-04 remove unused code
2021-03-04 store CFU scale and offset in arduino EEPROM
2021-03-08 update lockbar
2021-03-13 bugfix: turn off heaters in CANCEL
    This fixes #10.
2021-03-19 bugfix: play sound also returns with '$'
2021-03-19 calibration commands print '$' when done
2021-03-19 rename calibration 'scale'->'slope'
2021-04-28 add ability to get calibration values
2021-04-28 save and load calibration values works
2021-07-15 Add kitspace.yaml
2021-07-15 Put sensor gerbers into gerber folder
2021-07-15 Correct a URL in shield 008 BOM
2021-07-15 Make BOMs parse-able by Kitspace
2021-07-15 Add BOMs to kitspace.yaml

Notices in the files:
PCB/Sensor/Eagle/sensor_004.brd:
20150720 Licensed under CERN OHL v.1.2
parts and their libraries:
microbuilder: This work is placed in the public domain, and may be freely used for commercial and non-commercial work with the following conditions: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
Eagle_FPC_CONNECTOR_AND_FFC_CAB: Copyright: Würth Elektronik
